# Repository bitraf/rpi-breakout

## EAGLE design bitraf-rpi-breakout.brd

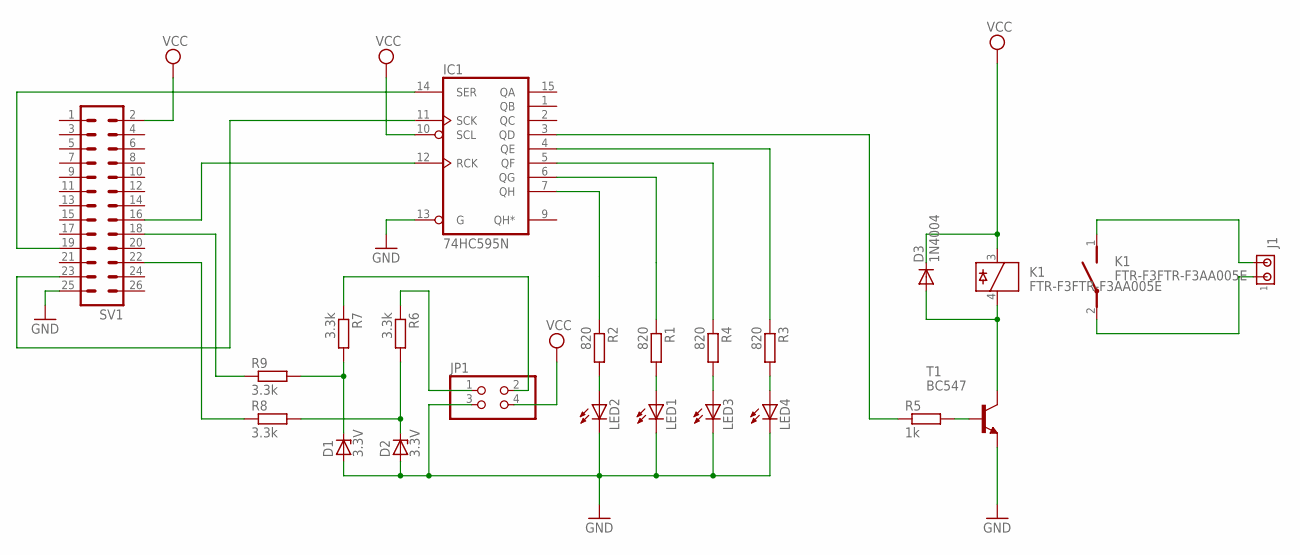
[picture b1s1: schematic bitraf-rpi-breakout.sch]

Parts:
D1, D2: 3.3V; ZDIO-7.5
D3: 1N4004; DO41-10
IC1: 74HC595N; DIL16
J1: MTA02-156; 1X2MTA
JP1: PINHD-2X2; 2X02
K1: FTR-F3FTR-F3AA005E; REED
LED1, LED2: LED3MM
LED3, LED4: LEDSML1206; SML1206
R1, R2: 820; 0204/7
R3, R4: 820; R1206
R5: 1k; 0204/7
R6, R7, R8, R9: 3.3k; 0204/7
SV1: ML26
T1: BC547; TO92

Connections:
GND: D1.A, D2.A, IC1.8 (GND), IC1.13 (G), JP1.3, LED1.K (C), LED2.K (C), LED3.C, LED4.C, SV1.25, T1.1 (E)
unnamed: LED2.A, R2.2
unnamed: LED1.A, R1.2
unnamed: IC1.5 (QF), R4.1
unnamed: IC1.7 (QH), R2.1
unnamed: IC1.6 (QG), R1.1
unnamed: R5.2, T1.2 (B)
unnamed: IC1.3 (QD), R5.1
unnamed: R8.1, SV1.22
unnamed: R9.1, SV1.18
unnamed: D1.C, R7.2, R9.2
unnamed: IC1.4 (QE), R3.1
unnamed: LED3.A, R4.2
unnamed: LED4.A, R3.2
unnamed: D3.A, K1.4, T1.3 (C)
unnamed: J1.1, K1.2
unnamed: J1.2, K1.1
unnamed: D2.C, R6.2, R8.2
unnamed: IC1.12 (RCK), SV1.16
unnamed: IC1.11 (SCK), SV1.23
unnamed: IC1.14 (SER), SV1.19
TTL_IN_1: JP1.2, R7.1
TTL_IN_2: JP1.1, R6.1
VCC: D3.C, IC1.10 (SCL), IC1.16 (VCC), JP1.4, K1.3, SV1.2

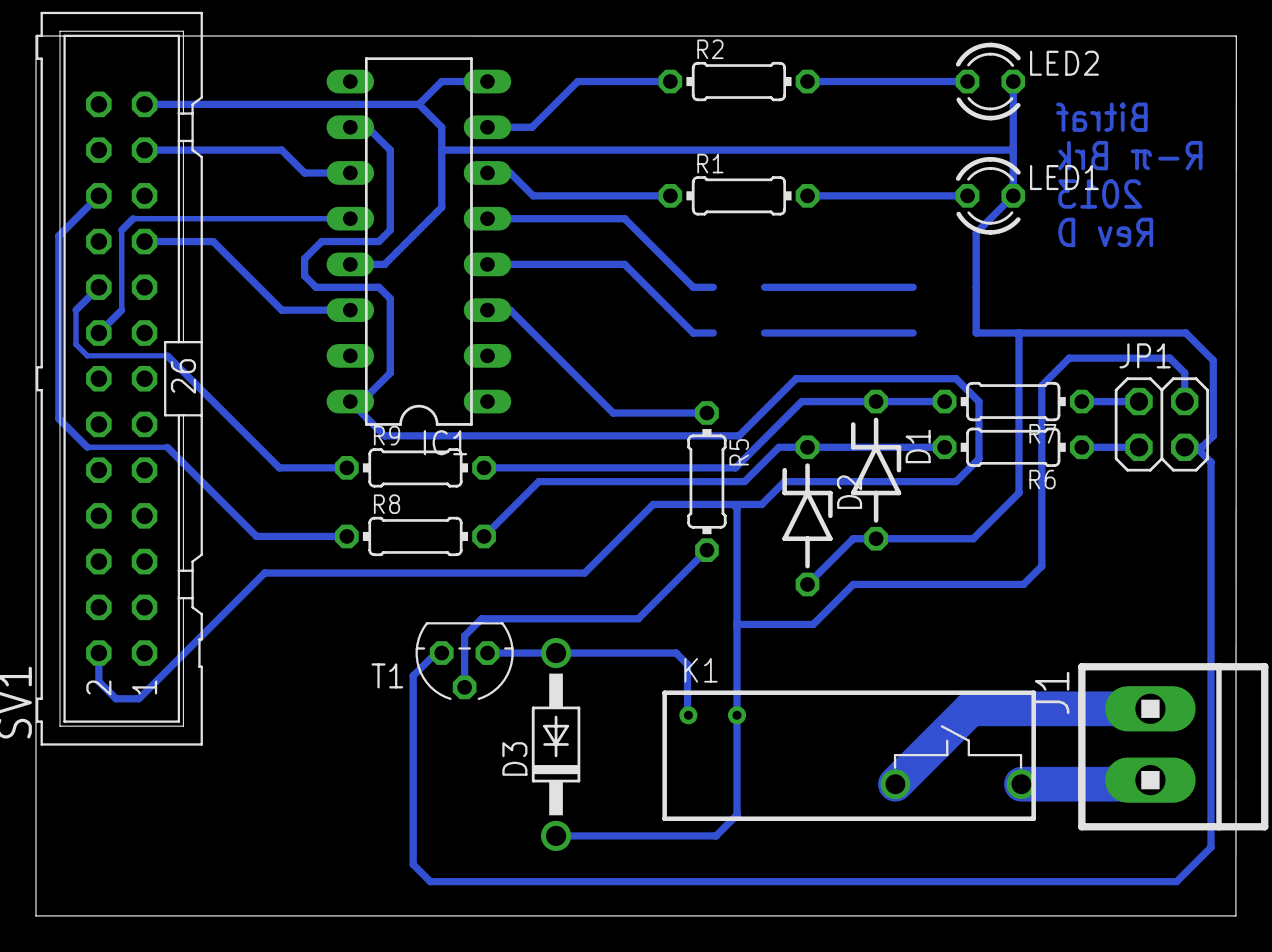
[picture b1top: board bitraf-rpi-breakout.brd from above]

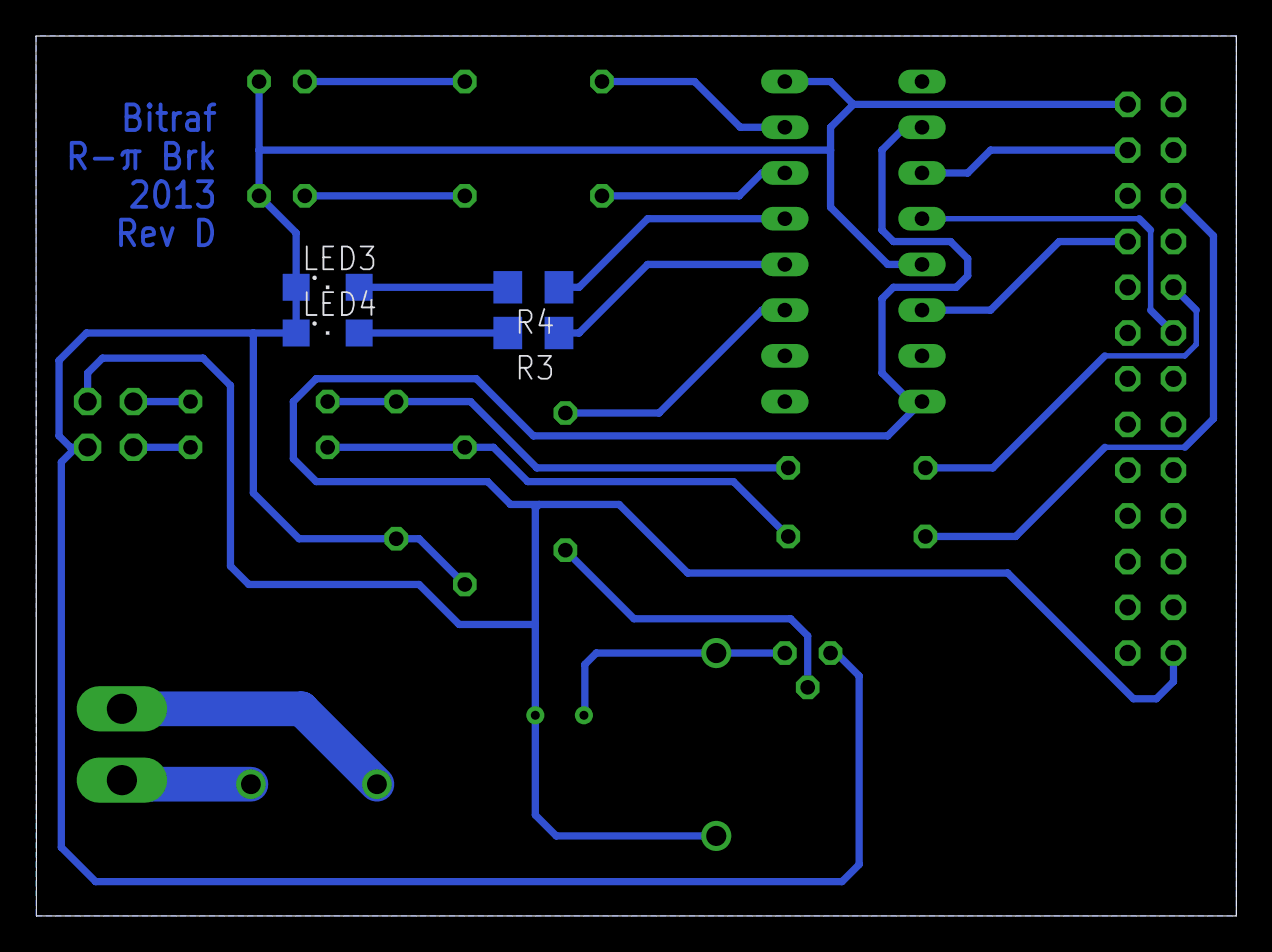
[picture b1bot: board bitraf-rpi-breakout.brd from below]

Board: 2 copper layers, 66.7 x 48.9 mm, 22 parts (4 on the bottom side), 24 nets.

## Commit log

2013-02-20 o Initial import.
2013-02-20 o With fill.
2013-02-20 nits
2013-02-20 Rev b.
2013-02-20 o Changing relay.
2013-02-20 o Relay was upside down.
2013-02-20 o Bigger isolate.
2013-02-20 o Updating relay footprint after test print.
2013-02-20 o Changing LED resistors from 330 to 820 ohm.
2013-02-20 o Rev D.
2013-02-20 o Bigger pads on relay.
